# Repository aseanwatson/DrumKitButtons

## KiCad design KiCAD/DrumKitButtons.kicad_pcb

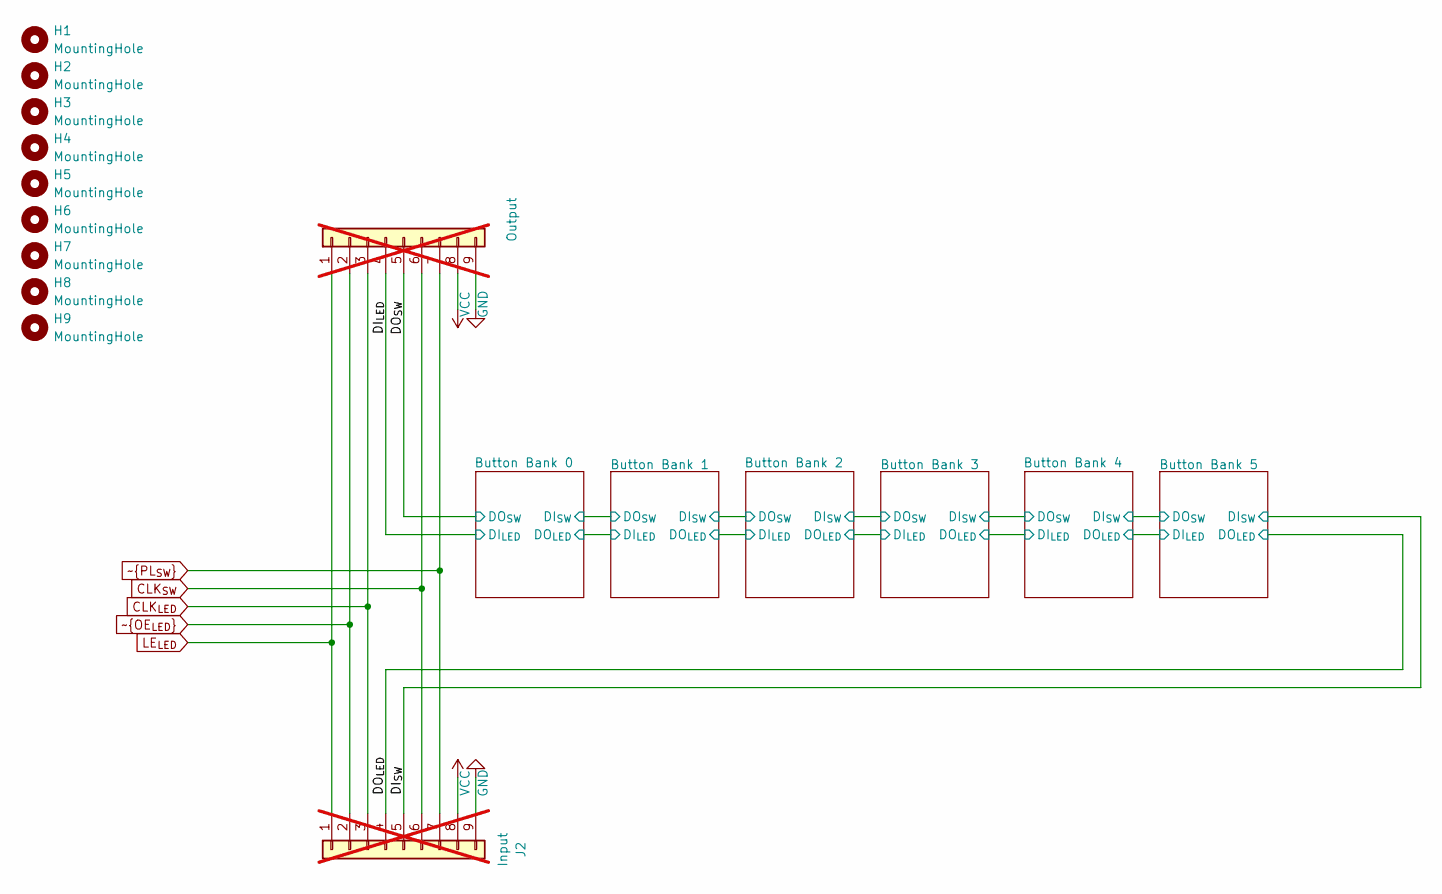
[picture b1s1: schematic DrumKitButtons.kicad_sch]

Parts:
H1, H2, H3, H4, H5, H6, H7, H8, H9: MountingHole; MountingHole_3.2mm_M3
J1: Output; PinHeader_1x09_P2.54mm_Vertical; not fitted
J2: Input; PinHeader_1x09_P2.54mm_Vertical; not fitted

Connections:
/DI_{LED}: J1.4; also elsewhere on the board
/DI_{SW}: J2.5; also elsewhere on the board
/DO_{LED}: J2.4; also elsewhere on the board
/DO_{SW}: J1.5; also elsewhere on the board
CLK_{LED}: J1.3, J2.3; also elsewhere on the board
CLK_{SW}: J1.6, J2.6; also elsewhere on the board
GND: J1.9, J2.9; also elsewhere on the board
LE_{LED}: J1.1, J2.1; also elsewhere on the board
VCC: J1.8, J2.8; also elsewhere on the board
~OE_{LED}: J1.2, J2.2; also elsewhere on the board
~PL_{SW}: J1.7, J2.7; also elsewhere on the board

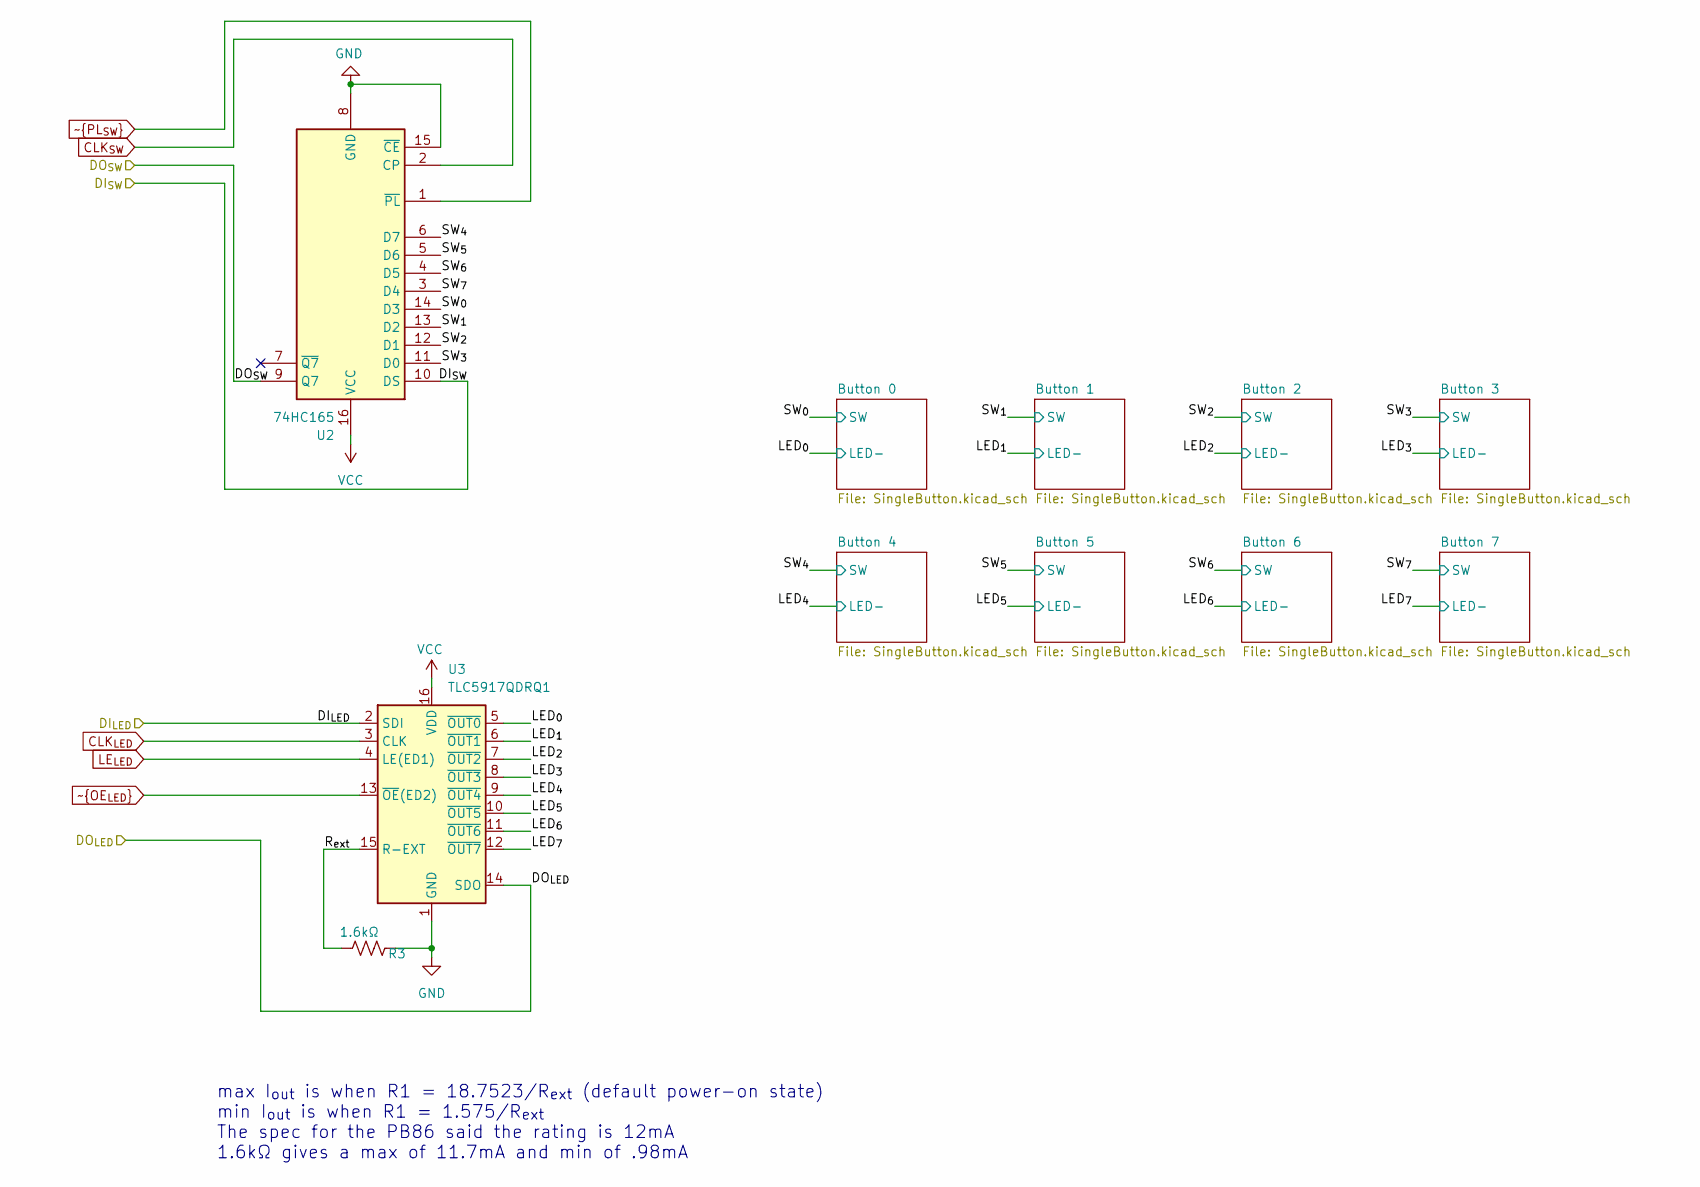
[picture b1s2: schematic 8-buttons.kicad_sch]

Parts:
R3: 1.6kΩ; R_0402_1005Metric; LCSC Part# C2906881
U2: 74HC165; SOIC-16_3.9x9.9mm_P1.27mm; LCSC Part# C5613
U3: TLC5917QDRQ1; SOIC-16_3.9x9.9mm_P1.27mm; LCSC Part# C2870661

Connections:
/Button Bank 0/DI_{SW}: U2.10 (DS); also elsewhere on the board
/Button Bank 0/DO_{LED}: U3.14 (SDO); also elsewhere on the board
/Button Bank 0/LED_{0}: U3.5 (~OUT0); also elsewhere on the board
/Button Bank 0/LED_{1}: U3.6 (~OUT1); also elsewhere on the board
/Button Bank 0/LED_{2}: U3.7 (~OUT2); also elsewhere on the board
/Button Bank 0/LED_{3}: U3.8 (~OUT3); also elsewhere on the board
/Button Bank 0/LED_{4}: U3.9 (~OUT4); also elsewhere on the board
/Button Bank 0/LED_{5}: U3.10 (~OUT5); also elsewhere on the board
/Button Bank 0/LED_{6}: U3.11 (~OUT6); also elsewhere on the board
/Button Bank 0/LED_{7}: U3.12 (~OUT7); also elsewhere on the board
/Button Bank 0/R_{ext}: R3.1, U3.15 (R-EXT)
/Button Bank 0/SW_{0}: U2.14 (D3); also elsewhere on the board
/Button Bank 0/SW_{1}: U2.13 (D2); also elsewhere on the board
/Button Bank 0/SW_{2}: U2.12 (D1); also elsewhere on the board
/Button Bank 0/SW_{3}: U2.11 (D0); also elsewhere on the board
/Button Bank 0/SW_{4}: U2.6 (D7); also elsewhere on the board
/Button Bank 0/SW_{5}: U2.5 (D6); also elsewhere on the board
/Button Bank 0/SW_{6}: U2.4 (D5); also elsewhere on the board
/Button Bank 0/SW_{7}: U2.3 (D4); also elsewhere on the board
/DI_{LED}: U3.2 (SDI); also elsewhere on the board
/DO_{SW}: U2.9 (Q7); also elsewhere on the board
CLK_{LED}: U3.3 (CLK); also elsewhere on the board
CLK_{SW}: U2.2 (CP); also elsewhere on the board
GND: R3.2, U2.8 (GND), U2.15 (~CE), U3.1 (GND); also elsewhere on the board
LE_{LED}: U3.4 (LE(ED1)); also elsewhere on the board
VCC: U2.16 (VCC), U3.16 (VDD); also elsewhere on the board
~OE_{LED}: U3.13 (~OE(ED2)); also elsewhere on the board
~PL_{SW}: U2.1 (~PL); also elsewhere on the board

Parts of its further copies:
R1, R18, R19, R36, R37: 1.6kΩ; R_0402_1005Metric; LCSC Part# C2906881
U1, U5, U8, U10, U11: TLC5917QDRQ1; SOIC-16_3.9x9.9mm_P1.27mm; LCSC Part# C2870661
U4, U6, U7, U9, U12: 74HC165; SOIC-16_3.9x9.9mm_P1.27mm; LCSC Part# C5613

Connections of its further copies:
/Button Bank 0/DI_{SW}: U4.9 (Q7); also elsewhere on the board
/Button Bank 0/DO_{LED}: U1.2 (SDI); also elsewhere on the board
/Button Bank 1/DI_{SW}: U4.10 (DS), U7.9 (Q7)
/Button Bank 1/DO_{LED}: U1.14 (SDO), U8.2 (SDI)
/Button Bank 1/LED_{0}: U1.5 (~OUT0); also elsewhere on the board
/Button Bank 1/LED_{1}: U1.6 (~OUT1); also elsewhere on the board
/Button Bank 1/LED_{2}: U1.7 (~OUT2); also elsewhere on the board
/Button Bank 1/LED_{3}: U1.8 (~OUT3); also elsewhere on the board
/Button Bank 1/LED_{4}: U1.9 (~OUT4); also elsewhere on the board
/Button Bank 1/LED_{5}: U1.10 (~OUT5); also elsewhere on the board
/Button Bank 1/LED_{6}: U1.11 (~OUT6); also elsewhere on the board
/Button Bank 1/LED_{7}: U1.12 (~OUT7); also elsewhere on the board
/Button Bank 1/R_{ext}: R1.1, U1.15 (R-EXT)
/Button Bank 1/SW_{0}: U4.14 (D3); also elsewhere on the board
/Button Bank 1/SW_{1}: U4.13 (D2); also elsewhere on the board
/Button Bank 1/SW_{2}: U4.12 (D1); also elsewhere on the board
/Button Bank 1/SW_{3}: U4.11 (D0); also elsewhere on the board
/Button Bank 1/SW_{4}: U4.6 (D7); also elsewhere on the board
/Button Bank 1/SW_{5}: U4.5 (D6); also elsewhere on the board
/Button Bank 1/SW_{6}: U4.4 (D5); also elsewhere on the board
/Button Bank 1/SW_{7}: U4.3 (D4); also elsewhere on the board
/Button Bank 2/DI_{SW}: U6.9 (Q7), U7.10 (DS)
/Button Bank 2/DO_{LED}: U5.2 (SDI), U8.14 (SDO)
/Button Bank 2/LED_{0}: U8.5 (~OUT0); also elsewhere on the board
/Button Bank 2/LED_{1}: U8.6 (~OUT1); also elsewhere on the board
/Button Bank 2/LED_{2}: U8.7 (~OUT2); also elsewhere on the board
/Button Bank 2/LED_{3}: U8.8 (~OUT3); also elsewhere on the board
/Button Bank 2/LED_{4}: U8.9 (~OUT4); also elsewhere on the board
/Button Bank 2/LED_{5}: U8.10 (~OUT5); also elsewhere on the board
/Button Bank 2/LED_{6}: U8.11 (~OUT6); also elsewhere on the board
/Button Bank 2/LED_{7}: U8.12 (~OUT7); also elsewhere on the board
/Button Bank 2/R_{ext}: R19.1, U8.15 (R-EXT)
/Button Bank 2/SW_{0}: U7.14 (D3); also elsewhere on the board
/Button Bank 2/SW_{1}: U7.13 (D2); also elsewhere on the board
/Button Bank 2/SW_{2}: U7.12 (D1); also elsewhere on the board
/Button Bank 2/SW_{3}: U7.11 (D0); also elsewhere on the board
/Button Bank 2/SW_{4}: U7.6 (D7); also elsewhere on the board
/Button Bank 2/SW_{5}: U7.5 (D6); also elsewhere on the board
/Button Bank 2/SW_{6}: U7.4 (D5); also elsewhere on the board
/Button Bank 2/SW_{7}: U7.3 (D4); also elsewhere on the board
/Button Bank 3/DI_{SW}: U6.10 (DS), U9.9 (Q7)
/Button Bank 3/DO_{LED}: U5.14 (SDO), U10.2 (SDI)
/Button Bank 3/LED_{0}: U5.5 (~OUT0); also elsewhere on the board
/Button Bank 3/LED_{1}: U5.6 (~OUT1); also elsewhere on the board
/Button Bank 3/LED_{2}: U5.7 (~OUT2); also elsewhere on the board
/Button Bank 3/LED_{3}: U5.8 (~OUT3); also elsewhere on the board
/Button Bank 3/LED_{4}: U5.9 (~OUT4); also elsewhere on the board
/Button Bank 3/LED_{5}: U5.10 (~OUT5); also elsewhere on the board
/Button Bank 3/LED_{6}: U5.11 (~OUT6); also elsewhere on the board
/Button Bank 3/LED_{7}: U5.12 (~OUT7); also elsewhere on the board
/Button Bank 3/R_{ext}: R18.1, U5.15 (R-EXT)
/Button Bank 3/SW_{0}: U6.14 (D3); also elsewhere on the board
/Button Bank 3/SW_{1}: U6.13 (D2); also elsewhere on the board
/Button Bank 3/SW_{2}: U6.12 (D1); also elsewhere on the board
/Button Bank 3/SW_{3}: U6.11 (D0); also elsewhere on the board
/Button Bank 3/SW_{4}: U6.6 (D7); also elsewhere on the board
/Button Bank 3/SW_{5}: U6.5 (D6); also elsewhere on the board
/Button Bank 3/SW_{6}: U6.4 (D5); also elsewhere on the board
/Button Bank 3/SW_{7}: U6.3 (D4); also elsewhere on the board
/Button Bank 4/DI_{SW}: U9.10 (DS), U12.9 (Q7)
/Button Bank 4/DO_{LED}: U10.14 (SDO), U11.2 (SDI)
/Button Bank 4/LED_{0}: U10.5 (~OUT0); also elsewhere on the board
/Button Bank 4/LED_{1}: U10.6 (~OUT1); also elsewhere on the board
/Button Bank 4/LED_{2}: U10.7 (~OUT2); also elsewhere on the board
/Button Bank 4/LED_{3}: U10.8 (~OUT3); also elsewhere on the board
/Button Bank 4/LED_{4}: U10.9 (~OUT4); also elsewhere on the board
/Button Bank 4/LED_{5}: U10.10 (~OUT5); also elsewhere on the board
/Button Bank 4/LED_{6}: U10.11 (~OUT6); also elsewhere on the board
/Button Bank 4/LED_{7}: U10.12 (~OUT7); also elsewhere on the board
/Button Bank 4/R_{ext}: R37.1, U10.15 (R-EXT)
/Button Bank 4/SW_{0}: U9.14 (D3); also elsewhere on the board
/Button Bank 4/SW_{1}: U9.13 (D2); also elsewhere on the board
/Button Bank 4/SW_{2}: U9.12 (D1); also elsewhere on the board
/Button Bank 4/SW_{3}: U9.11 (D0); also elsewhere on the board
/Button Bank 4/SW_{4}: U9.6 (D7); also elsewhere on the board
/Button Bank 4/SW_{5}: U9.5 (D6); also elsewhere on the board
/Button Bank 4/SW_{6}: U9.4 (D5); also elsewhere on the board
/Button Bank 4/SW_{7}: U9.3 (D4); also elsewhere on the board
/Button Bank 5/LED_{0}: U11.5 (~OUT0); also elsewhere on the board
/Button Bank 5/LED_{1}: U11.6 (~OUT1); also elsewhere on the board
/Button Bank 5/LED_{2}: U11.7 (~OUT2); also elsewhere on the board
/Button Bank 5/LED_{3}: U11.8 (~OUT3); also elsewhere on the board
/Button Bank 5/LED_{4}: U11.9 (~OUT4); also elsewhere on the board
/Button Bank 5/LED_{5}: U11.10 (~OUT5); also elsewhere on the board
/Button Bank 5/LED_{6}: U11.11 (~OUT6); also elsewhere on the board
/Button Bank 5/LED_{7}: U11.12 (~OUT7); also elsewhere on the board
/Button Bank 5/R_{ext}: R36.1, U11.15 (R-EXT)
/Button Bank 5/SW_{0}: U12.14 (D3); also elsewhere on the board
/Button Bank 5/SW_{1}: U12.13 (D2); also elsewhere on the board
/Button Bank 5/SW_{2}: U12.12 (D1); also elsewhere on the board
/Button Bank 5/SW_{3}: U12.11 (D0); also elsewhere on the board
/Button Bank 5/SW_{4}: U12.6 (D7); also elsewhere on the board
/Button Bank 5/SW_{5}: U12.5 (D6); also elsewhere on the board
/Button Bank 5/SW_{6}: U12.4 (D5); also elsewhere on the board
/Button Bank 5/SW_{7}: U12.3 (D4); also elsewhere on the board
/DI_{SW}: U12.10 (DS); also elsewhere on the board
/DO_{LED}: U11.14 (SDO); also elsewhere on the board
CLK_{LED}: U1.3 (CLK), U5.3 (CLK), U8.3 (CLK), U10.3 (CLK), U11.3 (CLK); also elsewhere on the board
CLK_{SW}: U4.2 (CP), U6.2 (CP), U7.2 (CP), U9.2 (CP), U12.2 (CP); also elsewhere on the board
GND: R1.2, R18.2, R19.2, R36.2, R37.2, U1.1 (GND), U4.8 (GND), U4.15 (~CE), U5.1 (GND), U6.8 (GND), U6.15 (~CE), U7.8 (GND), U7.15 (~CE), U8.1 (GND), U9.8 (GND), U9.15 (~CE), U10.1 (GND), U11.1 (GND), U12.8 (GND), U12.15 (~CE); also elsewhere on the board
LE_{LED}: U1.4 (LE(ED1)), U5.4 (LE(ED1)), U8.4 (LE(ED1)), U10.4 (LE(ED1)), U11.4 (LE(ED1)); also elsewhere on the board
VCC: U1.16 (VDD), U4.16 (VCC), U5.16 (VDD), U6.16 (VCC), U7.16 (VCC), U8.16 (VDD), U9.16 (VCC), U10.16 (VDD), U11.16 (VDD), U12.16 (VCC); also elsewhere on the board
~OE_{LED}: U1.13 (~OE(ED2)), U5.13 (~OE(ED2)), U8.13 (~OE(ED2)), U10.13 (~OE(ED2)), U11.13 (~OE(ED2)); also elsewhere on the board
~PL_{SW}: U4.1 (~PL), U6.1 (~PL), U7.1 (~PL), U9.1 (~PL), U12.1 (~PL); also elsewhere on the board

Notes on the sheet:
max I_{out} is when R1 = 18.7523/R_{ext} (default power-on state) min I_{out} is when R1 = 1.575/R_{ext} The spec for the PB86 said the rating is 12mA 1.6kΩ gives a max of 11.7mA and min of .98mA

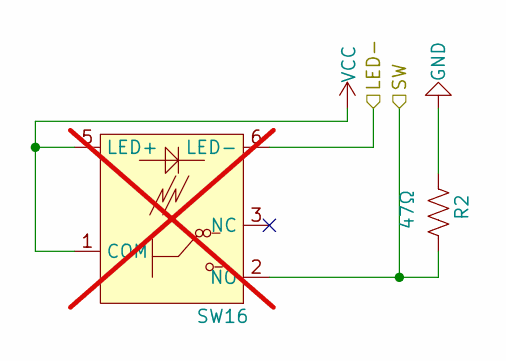
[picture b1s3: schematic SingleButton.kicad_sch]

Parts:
R2: 47Ω; R_0402_1005Metric; LCSC Part# C400522
SW16: PB86; not fitted

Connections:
/Button Bank 0/LED_{0}: SW16.6 (LED-); also elsewhere on the board
/Button Bank 0/SW_{0}: R2.2, SW16.2 (NO); also elsewhere on the board
GND: R2.1; also elsewhere on the board
VCC: SW16.1 (COM), SW16.5 (LED+); also elsewhere on the board

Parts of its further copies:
R4, R5, R6, R7, R8, R9, R10, R11, R12, R13, R14, R15, R16, R17, R20, R21, R22, R23, R24, R25, R26, R27, R28, R29, R30, R31, R32, R33, R34, R35, R38, R39, R40, R41, R42, R43, R44, R45, R46, R47, R48, R49, R50, R51, R52, R53, R54: 47Ω; R_0402_1005Metric; LCSC Part# C400522
SW1, SW2, SW3, SW4, SW5, SW6, SW7, SW8, SW9, SW10, SW11, SW12, SW13, SW14, SW15, SW17, SW18, SW19, SW20, SW21, SW22, SW23, SW24, SW25, SW26, SW27, SW28, SW29, SW30, SW31, SW32, SW33, SW34, SW35, SW36, SW37, SW38, SW39, SW40, SW41, SW42, SW43, SW44, SW45, SW46, SW47, SW48: PB86; not fitted

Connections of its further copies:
/Button Bank 0/LED_{1}: SW15.6 (LED-); also elsewhere on the board
/Button Bank 0/LED_{2}: SW14.6 (LED-); also elsewhere on the board
/Button Bank 0/LED_{3}: SW13.6 (LED-); also elsewhere on the board
/Button Bank 0/LED_{4}: SW11.6 (LED-); also elsewhere on the board
/Button Bank 0/LED_{5}: SW12.6 (LED-); also elsewhere on the board
/Button Bank 0/LED_{6}: SW10.6 (LED-); also elsewhere on the board
/Button Bank 0/LED_{7}: SW9.6 (LED-); also elsewhere on the board
/Button Bank 0/SW_{1}: R4.2, SW15.2 (NO); also elsewhere on the board
/Button Bank 0/SW_{2}: R5.2, SW14.2 (NO); also elsewhere on the board
/Button Bank 0/SW_{3}: R6.2, SW13.2 (NO); also elsewhere on the board
/Button Bank 0/SW_{4}: R7.2, SW11.2 (NO); also elsewhere on the board
/Button Bank 0/SW_{5}: R8.2, SW12.2 (NO); also elsewhere on the board
/Button Bank 0/SW_{6}: R9.2, SW10.2 (NO); also elsewhere on the board
/Button Bank 0/SW_{7}: R10.2, SW9.2 (NO); also elsewhere on the board
/Button Bank 1/LED_{0}: SW8.6 (LED-); also elsewhere on the board
/Button Bank 1/LED_{1}: SW7.6 (LED-); also elsewhere on the board
/Button Bank 1/LED_{2}: SW6.6 (LED-); also elsewhere on the board
/Button Bank 1/LED_{3}: SW4.6 (LED-); also elsewhere on the board
/Button Bank 1/LED_{4}: SW5.6 (LED-); also elsewhere on the board
/Button Bank 1/LED_{5}: SW3.6 (LED-); also elsewhere on the board
/Button Bank 1/LED_{6}: SW2.6 (LED-); also elsewhere on the board
/Button Bank 1/LED_{7}: SW1.6 (LED-); also elsewhere on the board
/Button Bank 1/SW_{0}: R11.2, SW8.2 (NO); also elsewhere on the board
/Button Bank 1/SW_{1}: R12.2, SW7.2 (NO); also elsewhere on the board
/Button Bank 1/SW_{2}: R13.2, SW6.2 (NO); also elsewhere on the board
/Button Bank 1/SW_{3}: R14.2, SW4.2 (NO); also elsewhere on the board
/Button Bank 1/SW_{4}: R15.2, SW5.2 (NO); also elsewhere on the board
/Button Bank 1/SW_{5}: R16.2, SW3.2 (NO); also elsewhere on the board
/Button Bank 1/SW_{6}: R17.2, SW2.2 (NO); also elsewhere on the board
/Button Bank 1/SW_{7}: R35.2, SW1.2 (NO); also elsewhere on the board
/Button Bank 2/LED_{0}: SW32.6 (LED-); also elsewhere on the board
/Button Bank 2/LED_{1}: SW31.6 (LED-); also elsewhere on the board
/Button Bank 2/LED_{2}: SW30.6 (LED-); also elsewhere on the board
/Button Bank 2/LED_{3}: SW29.6 (LED-); also elsewhere on the board
/Button Bank 2/LED_{4}: SW27.6 (LED-); also elsewhere on the board
/Button Bank 2/LED_{5}: SW28.6 (LED-); also elsewhere on the board
/Button Bank 2/LED_{6}: SW25.6 (LED-); also elsewhere on the board
/Button Bank 2/LED_{7}: SW26.6 (LED-); also elsewhere on the board
/Button Bank 2/SW_{0}: R20.2, SW32.2 (NO); also elsewhere on the board
/Button Bank 2/SW_{1}: R21.2, SW31.2 (NO); also elsewhere on the board
/Button Bank 2/SW_{2}: R22.2, SW30.2 (NO); also elsewhere on the board
/Button Bank 2/SW_{3}: R23.2, SW29.2 (NO); also elsewhere on the board
/Button Bank 2/SW_{4}: R24.2, SW27.2 (NO); also elsewhere on the board
/Button Bank 2/SW_{5}: R25.2, SW28.2 (NO); also elsewhere on the board
/Button Bank 2/SW_{6}: R26.2, SW25.2 (NO); also elsewhere on the board
/Button Bank 2/SW_{7}: R28.2, SW26.2 (NO); also elsewhere on the board
/Button Bank 3/LED_{0}: SW24.6 (LED-); also elsewhere on the board
/Button Bank 3/LED_{1}: SW23.6 (LED-); also elsewhere on the board
/Button Bank 3/LED_{2}: SW22.6 (LED-); also elsewhere on the board
/Button Bank 3/LED_{3}: SW20.6 (LED-); also elsewhere on the board
/Button Bank 3/LED_{4}: SW21.6 (LED-); also elsewhere on the board
/Button Bank 3/LED_{5}: SW18.6 (LED-); also elsewhere on the board
/Button Bank 3/LED_{6}: SW19.6 (LED-); also elsewhere on the board
/Button Bank 3/LED_{7}: SW17.6 (LED-); also elsewhere on the board
/Button Bank 3/SW_{0}: R27.2, SW24.2 (NO); also elsewhere on the board
/Button Bank 3/SW_{1}: R30.2, SW23.2 (NO); also elsewhere on the board
/Button Bank 3/SW_{2}: R29.2, SW22.2 (NO); also elsewhere on the board
/Button Bank 3/SW_{3}: R31.2, SW20.2 (NO); also elsewhere on the board
/Button Bank 3/SW_{4}: R33.2, SW21.2 (NO); also elsewhere on the board
/Button Bank 3/SW_{5}: R32.2, SW18.2 (NO); also elsewhere on the board
/Button Bank 3/SW_{6}: R34.2, SW19.2 (NO); also elsewhere on the board
/Button Bank 3/SW_{7}: R52.2, SW17.2 (NO); also elsewhere on the board
/Button Bank 4/LED_{0}: SW48.6 (LED-); also elsewhere on the board
/Button Bank 4/LED_{1}: SW46.6 (LED-); also elsewhere on the board
/Button Bank 4/LED_{2}: SW47.6 (LED-); also elsewhere on the board
/Button Bank 4/LED_{3}: SW45.6 (LED-); also elsewhere on the board
/Button Bank 4/LED_{4}: SW44.6 (LED-); also elsewhere on the board
/Button Bank 4/LED_{5}: SW43.6 (LED-); also elsewhere on the board
/Button Bank 4/LED_{6}: SW42.6 (LED-); also elsewhere on the board
/Button Bank 4/LED_{7}: SW41.6 (LED-); also elsewhere on the board
/Button Bank 4/SW_{0}: R38.2, SW48.2 (NO); also elsewhere on the board
/Button Bank 4/SW_{1}: R39.2, SW46.2 (NO); also elsewhere on the board
/Button Bank 4/SW_{2}: R41.2, SW47.2 (NO); also elsewhere on the board
/Button Bank 4/SW_{3}: R40.2, SW45.2 (NO); also elsewhere on the board
/Button Bank 4/SW_{4}: R43.2, SW44.2 (NO); also elsewhere on the board
/Button Bank 4/SW_{5}: R42.2, SW43.2 (NO); also elsewhere on the board
/Button Bank 4/SW_{6}: R44.2, SW42.2 (NO); also elsewhere on the board
/Button Bank 4/SW_{7}: R46.2, SW41.2 (NO); also elsewhere on the board
/Button Bank 5/LED_{0}: SW39.6 (LED-); also elsewhere on the board
/Button Bank 5/LED_{1}: SW40.6 (LED-); also elsewhere on the board
/Button Bank 5/LED_{2}: SW38.6 (LED-); also elsewhere on the board
/Button Bank 5/LED_{3}: SW37.6 (LED-); also elsewhere on the board
/Button Bank 5/LED_{4}: SW36.6 (LED-); also elsewhere on the board
/Button Bank 5/LED_{5}: SW34.6 (LED-); also elsewhere on the board
/Button Bank 5/LED_{6}: SW35.6 (LED-); also elsewhere on the board
/Button Bank 5/LED_{7}: SW33.6 (LED-); also elsewhere on the board
/Button Bank 5/SW_{0}: R45.2, SW39.2 (NO); also elsewhere on the board
/Button Bank 5/SW_{1}: R47.2, SW40.2 (NO); also elsewhere on the board
/Button Bank 5/SW_{2}: R48.2, SW38.2 (NO); also elsewhere on the board
/Button Bank 5/SW_{3}: R49.2, SW37.2 (NO); also elsewhere on the board
/Button Bank 5/SW_{4}: R51.2, SW36.2 (NO); also elsewhere on the board
/Button Bank 5/SW_{5}: R50.2, SW34.2 (NO); also elsewhere on the board
/Button Bank 5/SW_{6}: R53.2, SW35.2 (NO); also elsewhere on the board
/Button Bank 5/SW_{7}: R54.2, SW33.2 (NO); also elsewhere on the board
GND: R4.1, R5.1, R6.1, R7.1, R8.1, R9.1, R10.1, R11.1, R12.1, R13.1, R14.1, R15.1, R16.1, R17.1, R20.1, R21.1, R22.1, R23.1, R24.1, R25.1, R26.1, R27.1, R28.1, R29.1, R30.1, R31.1, R32.1, R33.1, R34.1, R35.1, R38.1, R39.1, R40.1, R41.1, R42.1, R43.1, R44.1, R45.1, R46.1, R47.1, R48.1, R49.1, R50.1, R51.1, R52.1, R53.1, R54.1; also elsewhere on the board
VCC: SW1.1 (COM), SW1.5 (LED+), SW2.1 (COM), SW2.5 (LED+), SW3.1 (COM), SW3.5 (LED+), SW4.1 (COM), SW4.5 (LED+), SW5.1 (COM), SW5.5 (LED+), SW6.1 (COM), SW6.5 (LED+), SW7.1 (COM), SW7.5 (LED+), SW8.1 (COM), SW8.5 (LED+), SW9.1 (COM), SW9.5 (LED+), SW10.1 (COM), SW10.5 (LED+), SW11.1 (COM), SW11.5 (LED+), SW12.1 (COM), SW12.5 (LED+), SW13.1 (COM), SW13.5 (LED+), SW14.1 (COM), SW14.5 (LED+), SW15.1 (COM), SW15.5 (LED+), SW17.1 (COM), SW17.5 (LED+), SW18.1 (COM), SW18.5 (LED+), SW19.1 (COM), SW19.5 (LED+), SW20.1 (COM), SW20.5 (LED+), SW21.1 (COM), SW21.5 (LED+), SW22.1 (COM), SW22.5 (LED+), SW23.1 (COM), SW23.5 (LED+), SW24.1 (COM), SW24.5 (LED+), SW25.1 (COM), SW25.5 (LED+), SW26.1 (COM), SW26.5 (LED+), SW27.1 (COM), SW27.5 (LED+), SW28.1 (COM), SW28.5 (LED+), SW29.1 (COM), SW29.5 (LED+), SW30.1 (COM), SW30.5 (LED+), SW31.1 (COM), SW31.5 (LED+), SW32.1 (COM), SW32.5 (LED+), SW33.1 (COM), SW33.5 (LED+), SW34.1 (COM), SW34.5 (LED+), SW35.1 (COM), SW35.5 (LED+), SW36.1 (COM), SW36.5 (LED+), SW37.1 (COM), SW37.5 (LED+), SW38.1 (COM), SW38.5 (LED+), SW39.1 (COM), SW39.5 (LED+), SW40.1 (COM), SW40.5 (LED+), SW41.1 (COM), SW41.5 (LED+), SW42.1 (COM), SW42.5 (LED+), SW43.1 (COM), SW43.5 (LED+), SW44.1 (COM), SW44.5 (LED+), SW45.1 (COM), SW45.5 (LED+), SW46.1 (COM), SW46.5 (LED+), SW47.1 (COM), SW47.5 (LED+), SW48.1 (COM), SW48.5 (LED+); also elsewhere on the board

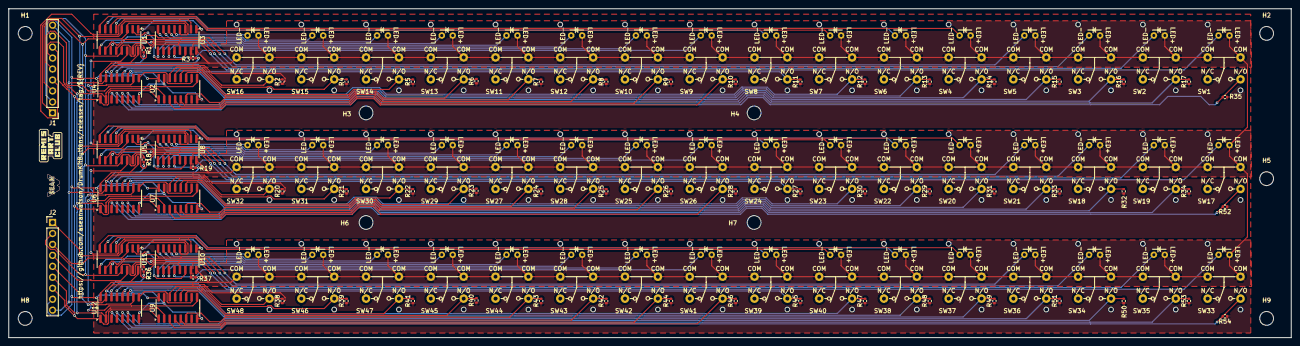
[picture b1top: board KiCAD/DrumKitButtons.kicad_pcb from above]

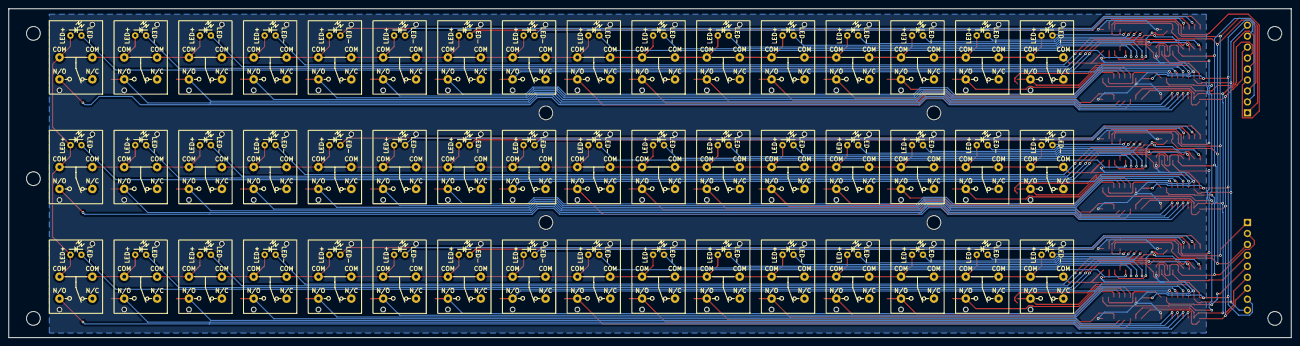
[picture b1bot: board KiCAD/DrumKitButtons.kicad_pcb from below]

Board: 2 copper layers, 297.2 x 76.2 mm, 125 parts (48 on the bottom side), 123 nets.

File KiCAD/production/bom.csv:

Designator,Footprint,Quantity,Value,LCSC Part #
"R1, R19, R2, R20, R37, R38",0402,6,1.6kΩ,
"R10, R11, R12, R13, R14, R15, R16, R17, R18, R21, R22, R23, R24, R25, R26, R27, R28, R29, R3, R30, R31, R32, R33, R34, R35, R36, R39, R4, R40, R41, R42, R43, R44, R45, R46, R47, R48, R49, R5, R50, R51, R52, R53, R54, R6, R7, R8, R9",0402,48,47Ω,
"U1, U10, U3, U5, U6, U9",SOIC-16_3.9x9.9mm_P1.27mm,6,74HC165,
"U11, U12, U2, U4, U7, U8",SOIC-16_3.9x9.9mm_P1.27mm,6,TLC5917QDRQ1,

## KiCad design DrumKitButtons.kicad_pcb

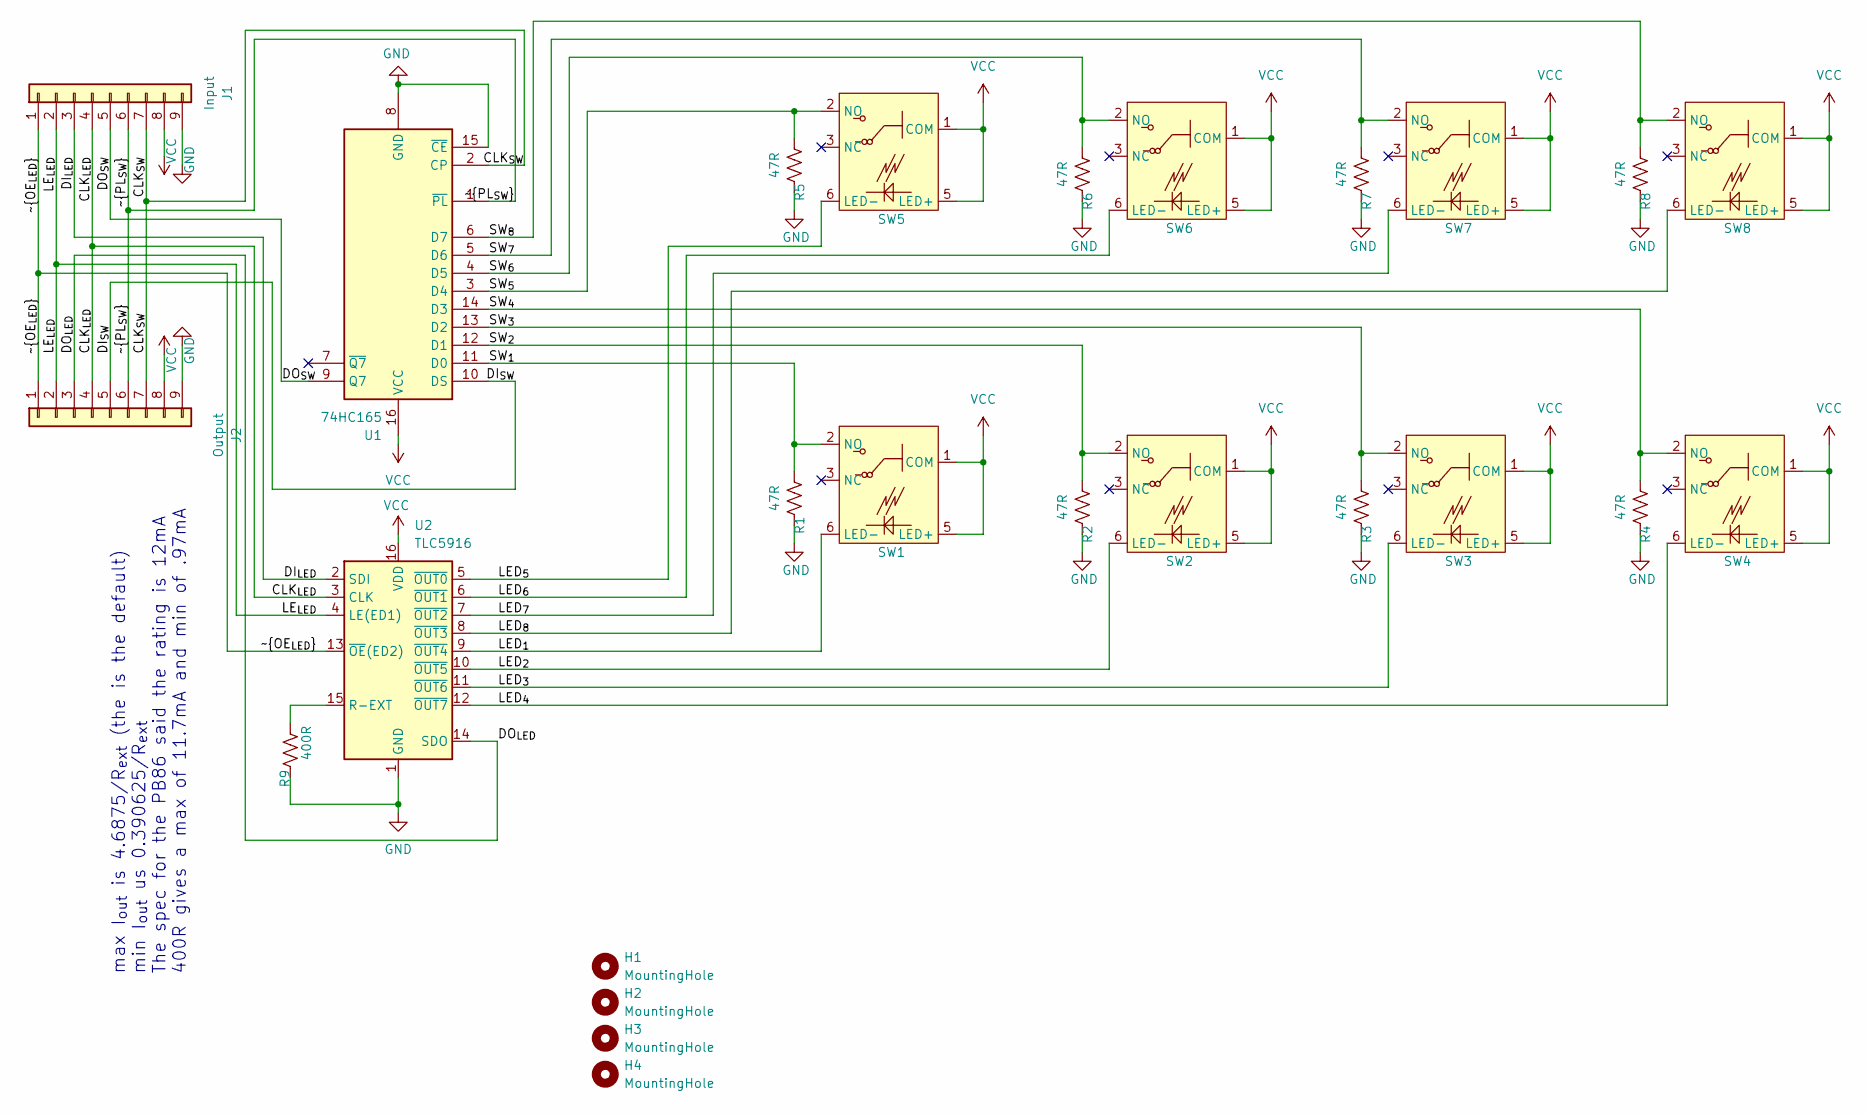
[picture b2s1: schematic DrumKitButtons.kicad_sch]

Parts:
H1, H2, H3, H4: MountingHole; MountingHole_3.2mm_M3
J1: Input; PinHeader_1x09_P2.54mm_Vertical
J2: Output; PinHeader_1x09_P2.54mm_Vertical
R1, R2, R3, R4, R5, R6, R7, R8: 47R; R_Axial_DIN0204_L3.6mm_D1.6mm_P5.08mm_Horizontal
R9: 400R; R_Axial_DIN0204_L3.6mm_D1.6mm_P5.08mm_Horizontal
SW1, SW2, SW3, SW4, SW5, SW6, SW7, SW8: PB86
U1: 74HC165; DIP-16_W7.62mm
U2: TLC5916; DIP-16_W7.62mm

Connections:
/CLK_{LED}: J1.4, J2.4, U2.3 (CLK)
/CLK_{SW}: J1.7, J2.7, U1.2 (CP)
/DI_{LED}: J1.3, U2.2 (SDI)
/DI_{SW}: J2.5, U1.10 (DS)
/DO_{LED}: J2.3, U2.14 (SDO)
/DO_{SW}: J1.5, U1.9 (Q7)
/LED_{1}: SW1.6 (LED-), U2.9 (~OUT4)
/LED_{2}: SW2.6 (LED-), U2.10 (~OUT5)
/LED_{3}: SW3.6 (LED-), U2.11 (~OUT6)
/LED_{4}: SW4.6 (LED-), U2.12 (~OUT7)
/LED_{5}: SW5.6 (LED-), U2.5 (~OUT0)
/LED_{6}: SW6.6 (LED-), U2.6 (~OUT1)
/LED_{7}: SW7.6 (LED-), U2.7 (~OUT2)
/LED_{8}: SW8.6 (LED-), U2.8 (~OUT3)
/LE_{LED}: J1.2, J2.2, U2.4 (LE(ED1))
/SW_{1}: R1.1, SW1.2 (NO), U1.11 (D0)
/SW_{2}: R2.1, SW2.2 (NO), U1.12 (D1)
/SW_{3}: R3.1, SW3.2 (NO), U1.13 (D2)
/SW_{4}: R4.1, SW4.2 (NO), U1.14 (D3)
/SW_{5}: R5.1, SW5.2 (NO), U1.3 (D4)
/SW_{6}: R6.1, SW6.2 (NO), U1.4 (D5)
/SW_{7}: R7.1, SW7.2 (NO), U1.5 (D6)
/SW_{8}: R8.1, SW8.2 (NO), U1.6 (D7)
/~OE_{LED}: J1.1, J2.1, U2.13 (~OE(ED2))
/~PL_{SW}: J1.6, J2.6, U1.1 (~PL)
GND: J1.9, J2.9, R1.2, R2.2, R3.2, R4.2, R5.2, R6.2, R7.2, R8.2, R9.2, U1.8 (GND), U1.15 (~CE), U2.1 (GND)
unnamed: R9.1, U2.15 (R-EXT)
VCC: J1.8, J2.8, SW1.1 (COM), SW1.5 (LED+), SW2.1 (COM), SW2.5 (LED+), SW3.1 (COM), SW3.5 (LED+), SW4.1 (COM), SW4.5 (LED+), SW5.1 (COM), SW5.5 (LED+), SW6.1 (COM), SW6.5 (LED+), SW7.1 (COM), SW7.5 (LED+), SW8.1 (COM), SW8.5 (LED+), U1.16 (VCC), U2.16 (VDD)

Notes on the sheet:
max I_{out} is 4.6875/R_{ext} (the is the default) min I_{out} us 0.390625/R_{ext} The spec for the PB86 said the rating is 12mA 400R gives a max of 11.7mA and min of .97mA

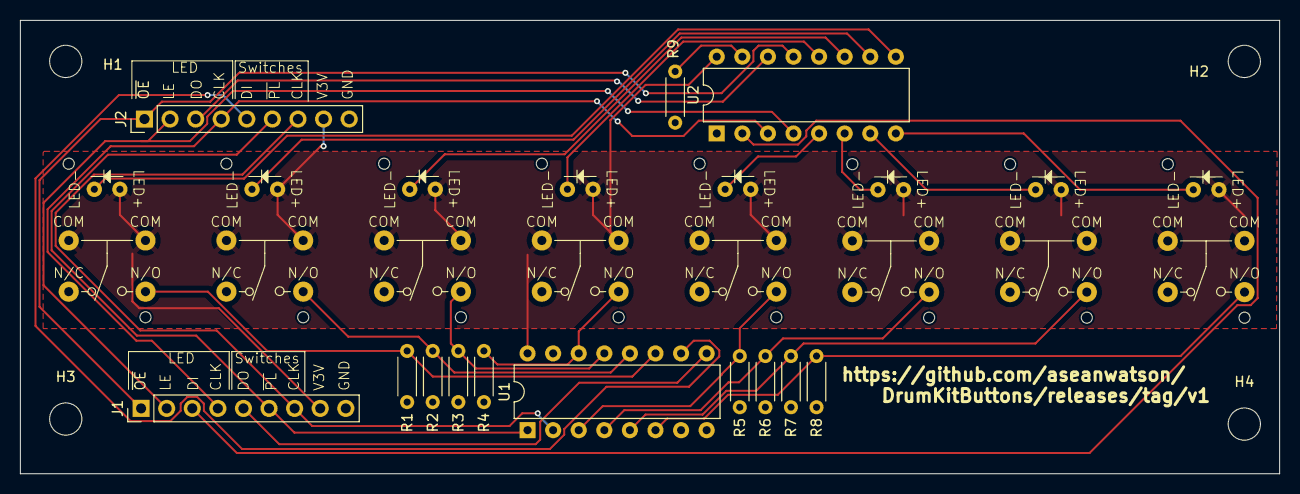
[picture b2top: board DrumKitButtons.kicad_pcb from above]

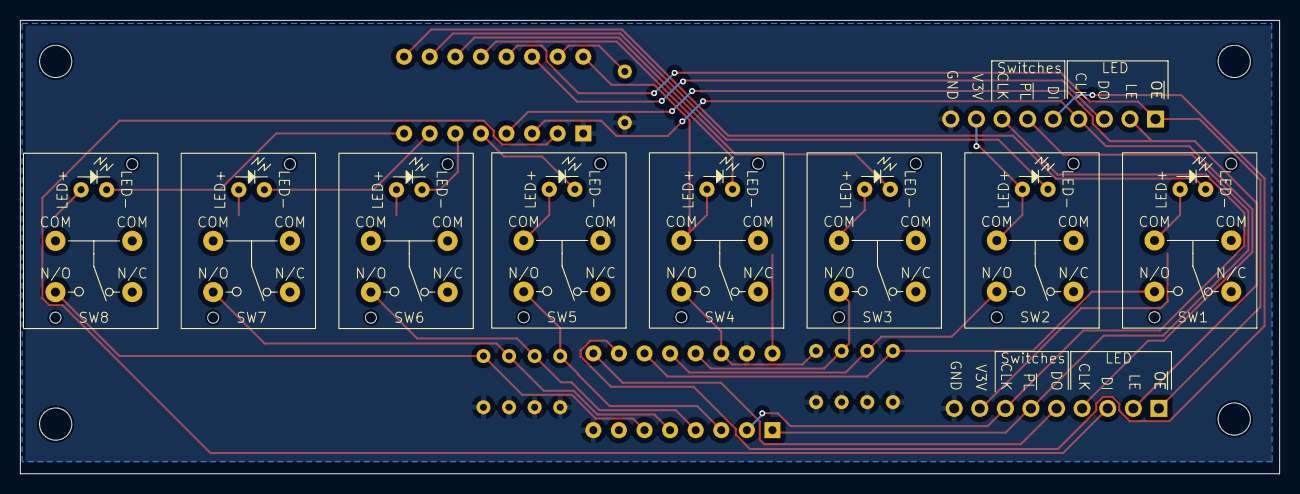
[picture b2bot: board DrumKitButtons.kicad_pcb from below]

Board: 2 copper layers, 125.0 x 45.0 mm, 25 parts (8 on the bottom side), 28 nets.

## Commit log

2024-11-10 First Draft of Schematic and PCB design
2024-11-11 Move 74HC165 to bottom
2024-11-11 use 3d models from https://github.com/ScharreSoft/PB86-footprints-and-3d-models
2024-11-11 fix #1
2024-11-12 next revision
2024-11-12 clean up traces; make VCC zone
2024-11-12 add URL; add extra dimension
2024-11-21 2 banks of 8 buttons; ICs on left
2024-11-22 move KiCAD data to its own folder
2024-11-22 address ERC error
2024-11-22 Put github URL in drawing sheet
2024-11-22 First crack at GitHub actions
2024-11-22 fix issues in kicad.yml
2024-11-22 Try to get kicad.yml working
    * fork the action to:
    * use `apt-get` rather than `apt`
    * give the `--yes` argument to `apt-get install`
    * `git describe` was failing; use `git describe --always` to do a better job.
2024-11-22 We need history for `git describe` to work.
2024-11-22 Upgrade to latest actions/checkout and actions/upload-artifact
2024-11-22 we don't need --dirty=-dirty on git describe
2024-11-25 fix DRC errors
2024-11-26 include *-lib-table files
2024-11-26 used setup-kicad@v1.1
2024-11-26 Upload after each step
2024-11-26 Revert "Upload after each step"
    This reverts commit ea9c0ddd6a74c0875bf0b148d14ecec8c13eb54e.
2024-11-26 Add more CI outputs
    * board-front.pdf / board-back.pdf rather than board.pdf
    * board-full.step / board-back.step
2024-11-26 Change {x,y} to * wildcard
2024-11-27 elimiate vias
2024-11-27 fill zones
2024-11-27 clean up button labels; keep trace out of mounting screw holes
2024-11-28 Change layer order in board PDF build
2024-11-30 clean up spurious wire in schematic
2024-11-30 reannotate schematic; line things up better
2024-11-30 reorder buttons/leds
2024-11-30 remove autosave
2025-02-26 make 3 rows in schema; break single button out to its own kicad_sch
2025-02-26 Rough outline of single row
2025-02-26 fix misplaced wire in schematic
2025-02-27 3 rows of 16 buttons; SMT
2025-02-27 Revert "3 rows of 16 buttons; SMT"
    This reverts commit c08e4dc0c350e57a2ca7329c2459be699e742724.
2025-03-02 Rework single row to use more of the vertical space between button contacts.
2025-03-02 remove short in schematic
2025-03-04 clean up SingleButton schematic
2025-03-04 Add 3 rows again
2025-03-05 edge cuts and mounting holes
2025-03-05 DNP for headers; switch 5916->5917
2025-03-06 fix ERC/DRC violations
2025-03-06 remove production folder; it's built
2025-03-06 remove DrumKitButtons.kicad_pcb.zip; it's built
2025-03-06 Switch to KiCAD 9.0
